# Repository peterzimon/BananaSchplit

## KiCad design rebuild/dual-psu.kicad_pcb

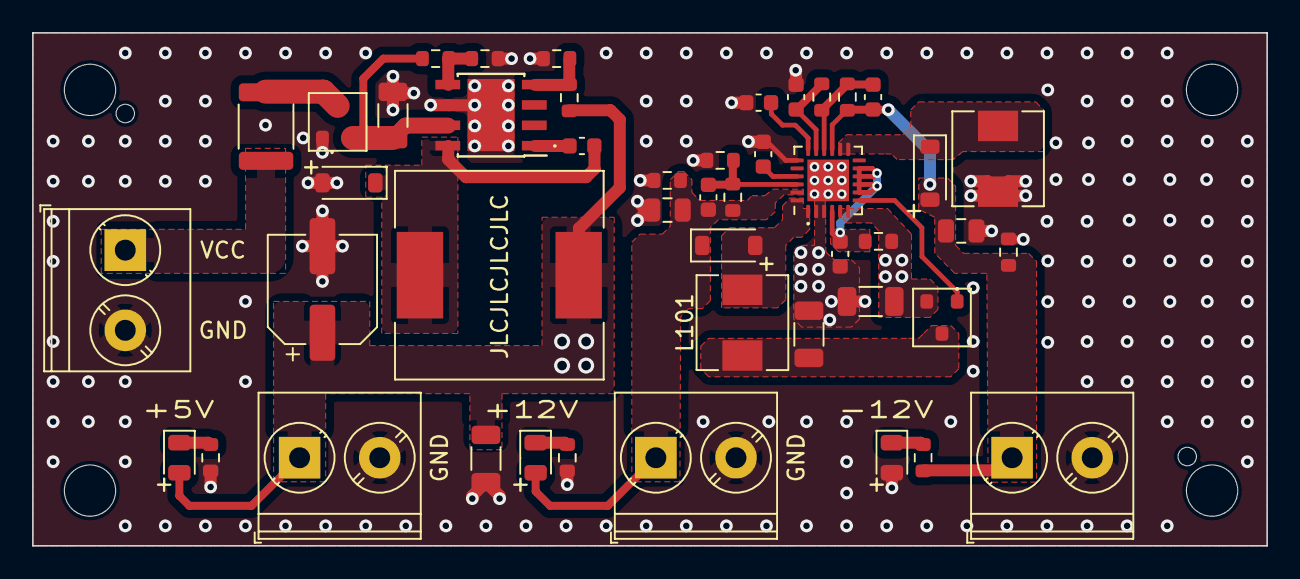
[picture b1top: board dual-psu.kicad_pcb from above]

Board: 4 copper layers, 77.0 x 32.0 mm, 50 parts (0 on the bottom side), 24 nets.

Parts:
C101, C102, C103, C107: 10u; C_1206_3216Metric
C104: 100n; C_0603_1608Metric
C105, C106: 10n; C_0603_1608Metric
C108: 6p8; C_0603_1608Metric
C109: 8p2; C_0603_1608Metric
C110: 220u; CP_Elec_6.3x7.7
C111: 220n; C_0603_1608Metric
C112, C113: 22u; C_0805_2012Metric
C114: 4n7; C_0603_1608Metric
D101, D102, D103: B5819W; D_SOD-123
D104: RED; LED_0805_2012Metric
D105: GREEN; LED_0805_2012Metric
D106: YELLOW; LED_0805_2012Metric
F101: 500mA; Fuse_1812_4532Metric
H101, H102, H103, H104: MountingHole; MountingHole_3.2mm_M3
J101, J102, J103, J104: Screw_Terminal_01x02; TerminalBlock_Phoenix_PT-1,5-2-5.0-H_1x02_P5.00mm_Horizontal
L101, L103: 10u; L_Sunlord_MWSA0518S
L102: 47u; L_Sunlord_SWRB1204S
Q101, Q102: AO3401A; SOT-23
R101: 100; R_0603_1608Metric
R102, R103, R106: 100k; R_0603_1608Metric
R104, R107: 1M; R_0603_1608Metric
R105: 110k; R_0603_1608Metric
R108: 10k; R_0603_1608Metric
R109: 3k3; R_0603_1608Metric
R110, R111: 12k; R_0603_1608Metric
R112: 1k5; R_0603_1608Metric
R113: 4k3; R_0603_1608Metric
R114: 5k1; R_0603_1608Metric
U101: TPS65131RGER; QFN-24-1EP_4x4mm_P0.5mm_EP2.6x2.6mm
U102: TPS5430DDA; TI_SO-PowerPAD-8_ThermalVias

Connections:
+5V: C101.1, C107.1, C110.1, D104.2 (A), J103.1, L102.2, Q102.2 (S), R101.2, R108.2, U101.5 (INN_1), U101.6 (INN_2)
+12V: C108.1, C113.1, D101.1 (K), D105.2 (A), J102.1, R104.2, R111.2, U101.23 (VPOS)
-12V: C109.2, C112.1, D103.2 (A), J104.1, R107.1, R110.2, R114.1, U101.15 (VNEG)
GND: C101.2, C102.2, C103.2, C104.2, C106.2, C107.2, C110.2, C111.2, C112.2, C113.2, C114.2, D102.2 (A), D106.2 (A), J101.2, J102.2, J103.2, J104.2, L103.2, Q101.1 (G), R103.1, R105.1, R109.1, R110.1, R111.1, R112.1, R113.1, U101.2 (PGND_1), U101.3 (PGND_2), U101.19 (AGND), U101.25 (POWERPAD), U102.6 (GND), U102.9 (GNDPAD)
unnamed: D101.2 (A), L101.2, U101.1 (INP_1), U101.24 (INP_2)
unnamed: C105.2, D102.1 (K), L102.1, U102.8 (PH)
unnamed: D103.1 (K), L103.1, U101.13 (OUTN_1), U101.14 (OUTN_2)
unnamed: D104.1 (K), R112.2
unnamed: D105.1 (K), R113.2
unnamed: D106.1 (K), R114.2
unnamed: F101.1, Q101.3 (D)
unnamed: C102.1, Q101.2 (S), R102.2, U102.7 (VIN)
unnamed: C103.1, L101.1, Q102.3 (D)
unnamed: Q102.1 (G), U101.7 (BSW)
unnamed: C114.1, U101.18 (CN)
unnamed: C106.1, U101.21 (CP)
unnamed: C104.1, R101.1, U101.4 (VIN), U101.8 (ENP), U101.9 (PSP), U101.10 (ENN), U101.11 (PSN)
unnamed: C109.1, R106.1, R107.2, U101.16 (FBN)
unnamed: C108.2, R104.1, R105.2, U101.22 (FBP)
unnamed: C111.1, R106.2, U101.17 (VREF)
unnamed: C105.1, U102.1 (BOOT)
unnamed: R102.1, R103.2, U102.5 (EN)
PSU_FB: R108.1, R109.2, U102.4 (VSENSE)
VCC: F101.2, J101.1

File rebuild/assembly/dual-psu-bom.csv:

Comment,Designator,Footprint,LCSC
"10u","C101,C102,C103,C107","Capacitor_SMD:C_1206_3216Metric","C13585"
"100n","C104","Capacitor_SMD:C_0603_1608Metric","C14663"
"10n","C105,C106","Capacitor_SMD:C_0603_1608Metric","C57112"
"6p8","C108","Capacitor_SMD:C_0603_1608Metric","C1679"
"8p2","C109","Capacitor_SMD:C_0603_1608Metric","C1685"
"220u","C110","Capacitor_SMD:CP_Elec_6.3x7.7","C127327"
"220n","C111","Capacitor_SMD:C_0603_1608Metric","C21120"
"22u","C112,C113","Capacitor_SMD:C_0805_2012Metric","C45783"
"4n7","C114","Capacitor_SMD:C_0603_1608Metric","C53987"
"B5819W","D101,D102,D103","Diode_SMD:D_SOD-123","C8598"
"RED","D104","LED_SMD:LED_0805_2012Metric","C84256"
"GREEN","D105","LED_SMD:LED_0805_2012Metric","C2297"
"YELLOW","D106","LED_SMD:LED_0805_2012Metric","C2296"
"500mA","F101","Fuse:Fuse_1812_4532Metric",""
"10u","L101,L103","Inductor_SMD:L_Sunlord_MWSA0518S","C181721"
"47u","L102","Inductor_SMD:L_Sunlord_SWRB1204S","C169398"
"AO3401A","Q101,Q102","PCM_Package_TO_SOT_SMD_AKL:SOT-23","C15127"
"100","R101","Resistor_SMD:R_0603_1608Metric","C22775"
"100k","R102,R103,R106","Resistor_SMD:R_0603_1608Metric","C25803"
"1M","R104,R107","Resistor_SMD:R_0603_1608Metric","C22935"
"110k","R105","Resistor_SMD:R_0603_1608Metric","C25805"
"10k","R108","Resistor_SMD:R_0603_1608Metric","C25804"
"3k3","R109","Resistor_SMD:R_0603_1608Metric","C22978"
"12k","R110,R111","Resistor_SMD:R_0603_1608Metric","C22790"
"1k5","R112","Resistor_SMD:R_0603_1608Metric","C22843"
"4k3","R113","Resistor_SMD:R_0603_1608Metric","C23159"
"5k1","R114","Resistor_SMD:R_0603_1608Metric","C23186"
"TPS65131RGER","U101","Package_DFN_QFN:QFN-24-1EP_4x4mm_P0.5mm_EP2.6x2.6mm","C87663"
"TPS5430DDA","U102","Package_SO:TI_SO-PowerPAD-8_ThermalVias","C9864"

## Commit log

2023-10-27 Rebuilt on separate sheet
